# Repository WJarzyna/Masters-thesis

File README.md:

# Praca-inzynierska
Sterownik silnika synchronicznego ze zmiennym momentem magnetycznym wirnika

Poniższe repozytorium zawiera materiały dotyczące budowy sterownika silnika. Docelowo silnik ma powstać na bazie zmodyfikowanego alternatora Magneti Marelli 14V/55A i udostępniać następujące metody sterowania:
- z wykorzystaniem czujników Halla
- z wykorzystaniem sygnału BEMF
- przez pomiar prądów fazowych

Założenia projektowe sterownika:
- budowa modularna - płyta główna + 3 płyty z półmostkami
- separacja galwaniczna części sterowania i mocy
- sterowanie poprzez mikrokontroler Raspberry Pi RP2040

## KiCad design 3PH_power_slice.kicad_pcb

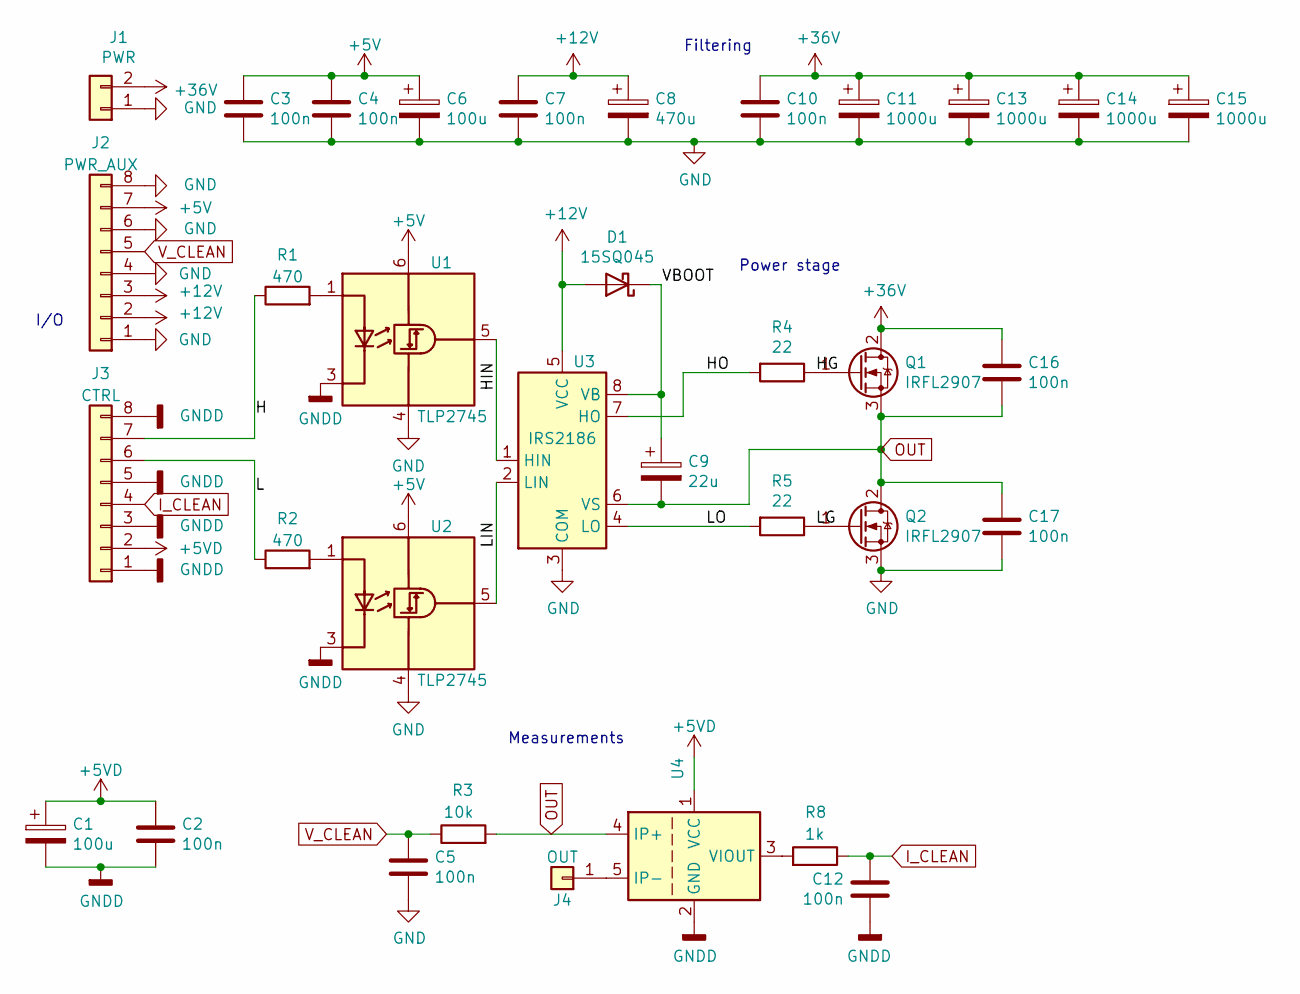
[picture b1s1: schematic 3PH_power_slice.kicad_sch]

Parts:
C1, C6: 100u; CP_Radial_D5.0mm_P2.50mm
C2, C3, C4, C5, C7, C10, C12, C16, C17: 100n; C_0805_2012Metric
C8: 470u; CP_Radial_D10.0mm_P5.00mm
C9: 22u; CP_Radial_D5.0mm_P2.50mm
C11, C13, C14, C15: 1000u; CP_Radial_D12.5mm_P5.00mm
D1: 15SQ045; D_P600_R-6_P12.70mm_Horizontal
J1: PWR; XT90PB
J2: PWR_AUX; PinHeader_1x08_P2.54mm_Vertical
J3: CTRL; PinHeader_1x08_P2.54mm_Vertical
J4: OUT; XT90PB_1Pin
Q1, Q2: IRFL2907; TO-247-3_Vertical
R1, R2: 470; R_0805_2012Metric
R3: 10k; R_0805_2012Metric
R4, R5: 22; R_Axial_DIN0411_L9.9mm_D3.6mm_P12.70mm_Horizontal
R8: 1k; R_0805_2012Metric
U1, U2: TLP2745; SO-5_4.4x3.6mm_P1.27mm
U3: IRS2186; DIP-8_W7.62mm_LongPads
U4: ACS758xCB-100B-PFF; Allegro_CB_PFF

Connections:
+5V: C3.1, C4.1, C6.1, J2.7, U1.6 (VDD), U2.6 (VDD)
+5VD: C1.1, C2.1, J3.2, U4.1 (VCC)
+12V: C7.1, C8.1, D1.2 (A), J2.2, J2.3, U3.5 (VCC)
+36V: C10.1, C11.1, C13.1, C14.1, C15.1, C16.1, J1.2, Q1.2 (D)
/H: J3.7, R1.1
/HG: Q1.1 (G), R4.1
/HIN: U1.5 (VO), U3.1 (HIN)
/HO: R4.2, U3.7 (HO)
/L: J3.6, R2.1
/LG: Q2.1 (G), R5.1
/LIN: U2.5 (VO), U3.2 (LIN)
/LO: R5.2, U3.4 (LO)
/VBOOT: C9.1, D1.1 (K), U3.8 (VB)
GND: C3.2, C4.2, C5.2, C6.2, C7.2, C8.2, C10.2, C11.2, C13.2, C14.2, C15.2, C17.2, J1.1, J2.1, J2.4, J2.6, J2.8, Q2.3 (S), U1.4 (GND), U2.4 (GND), U3.3 (COM)
GNDD: C1.2, C2.2, C12.2, J3.1, J3.3, J3.5, J3.8, U1.3 (K), U2.3 (K), U4.2 (GND)
I_CLEAN: C12.1, J3.4, R8.1
unnamed: J4.1, U4.5 (IP-)
unnamed: R1.2, U1.1 (A)
unnamed: R2.2, U2.1 (A)
unnamed: R8.2, U4.3 (VIOUT)
OUT: C9.2, C16.2, C17.1, Q1.3 (S), Q2.2 (D), R3.2, U3.6 (VS), U4.4 (IP+)
V_CLEAN: C5.1, J2.5, R3.1

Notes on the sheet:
I/O
Filtering
Measurements
Power stage

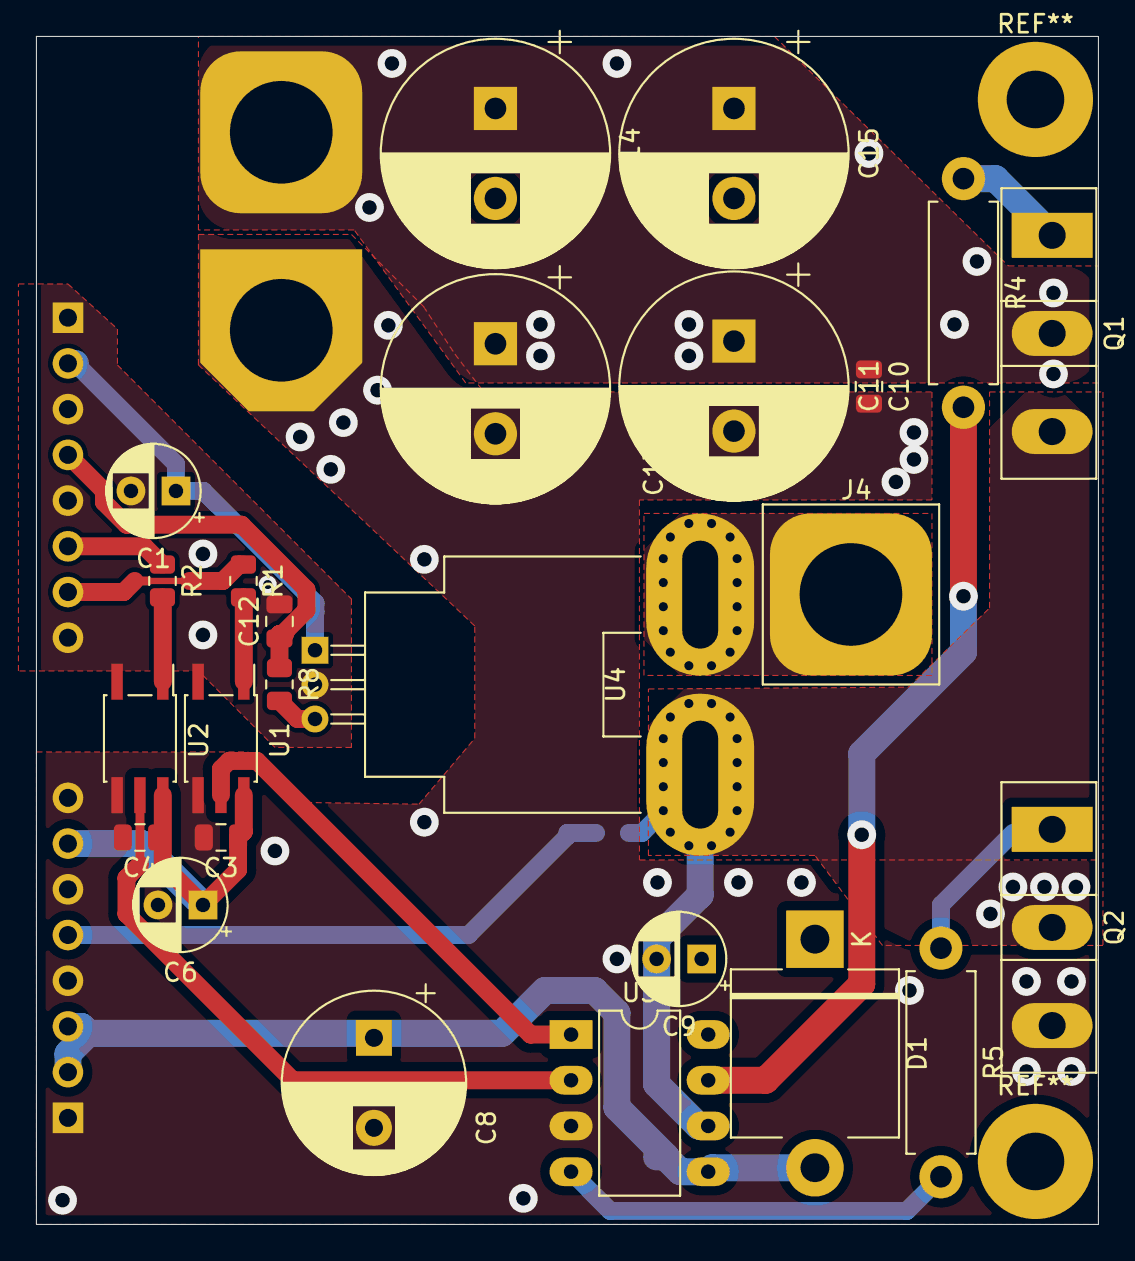
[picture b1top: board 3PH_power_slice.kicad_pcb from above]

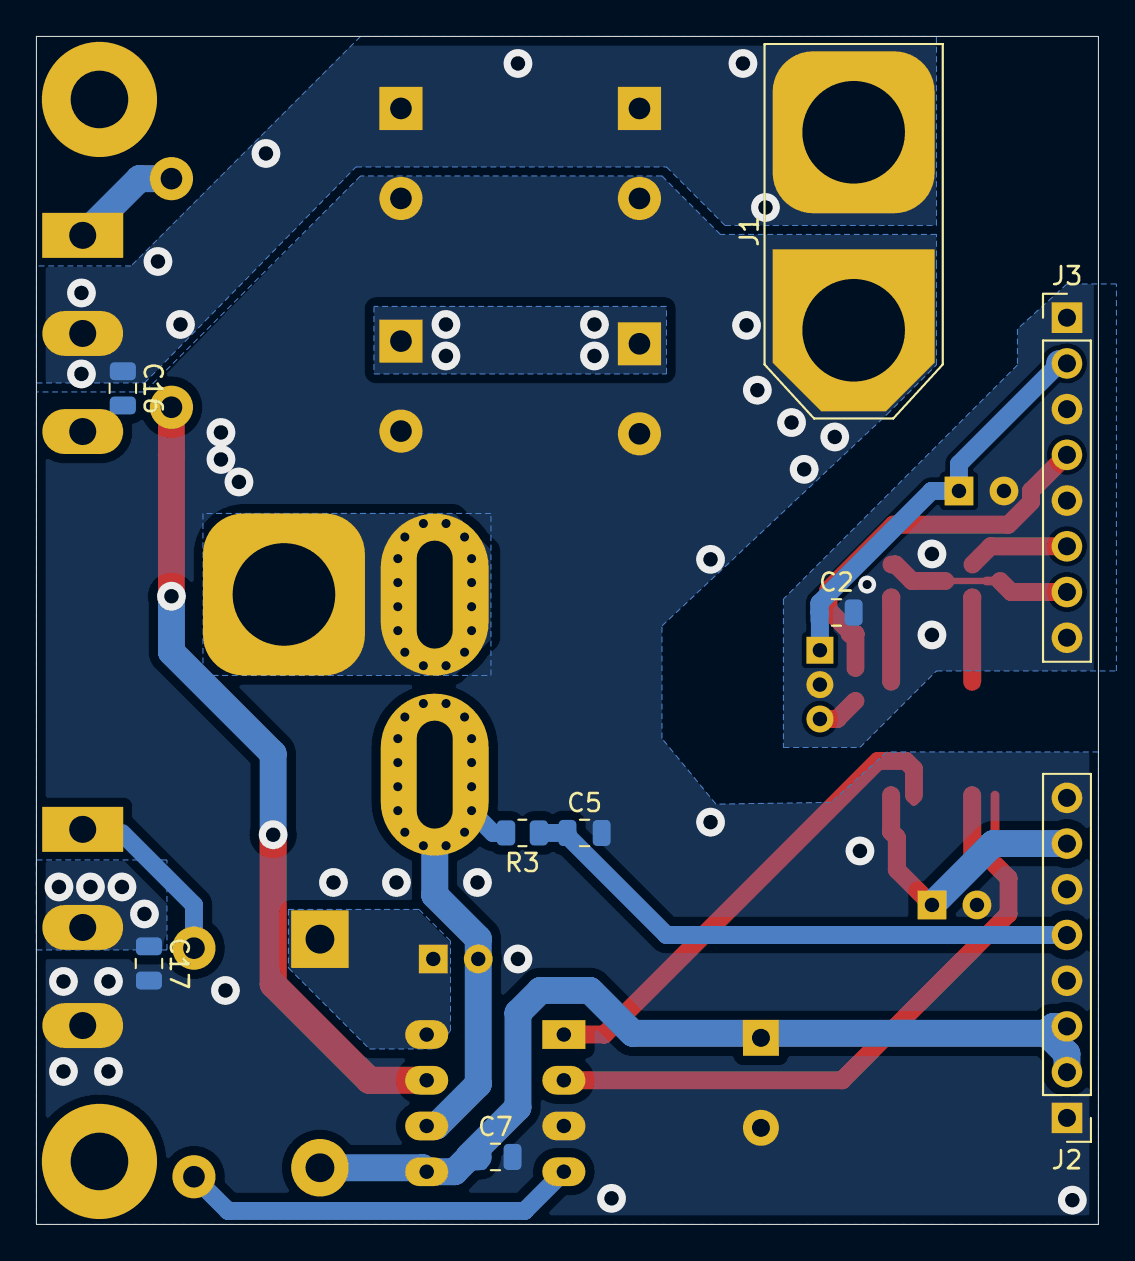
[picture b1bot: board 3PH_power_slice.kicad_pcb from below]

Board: 2 copper layers, 59.0 x 66.0 mm, 34 parts (9 on the bottom side), 22 nets.

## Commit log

2022-07-31 Dodanie dotychczas zgromadzonych materialow
2022-10-13 Migracja do KiCADa 6, schemat i PCB półmostka
2022-10-21 porzadki, przeniesienie projektu w IDE, zmiana stopnia mocy
2022-10-28 nowy protokol komunikacyjny, tryb półślepy, rewers, unifikacja tabeli komutacji
2022-10-30 Dzialajace przerwania
2022-10-30 Obliczenia predkosci in-place, zabezpieczenia
2022-10-31 PID - prototyp. Praca w petli zamknietej, regulacja predkosci
2022-12-01 stable hall with PID
2023-11-29 general refactor
2023-11-29 remote PID tuning
2024-03-08 Repo cleanup
2024-03-08 further cleanup
